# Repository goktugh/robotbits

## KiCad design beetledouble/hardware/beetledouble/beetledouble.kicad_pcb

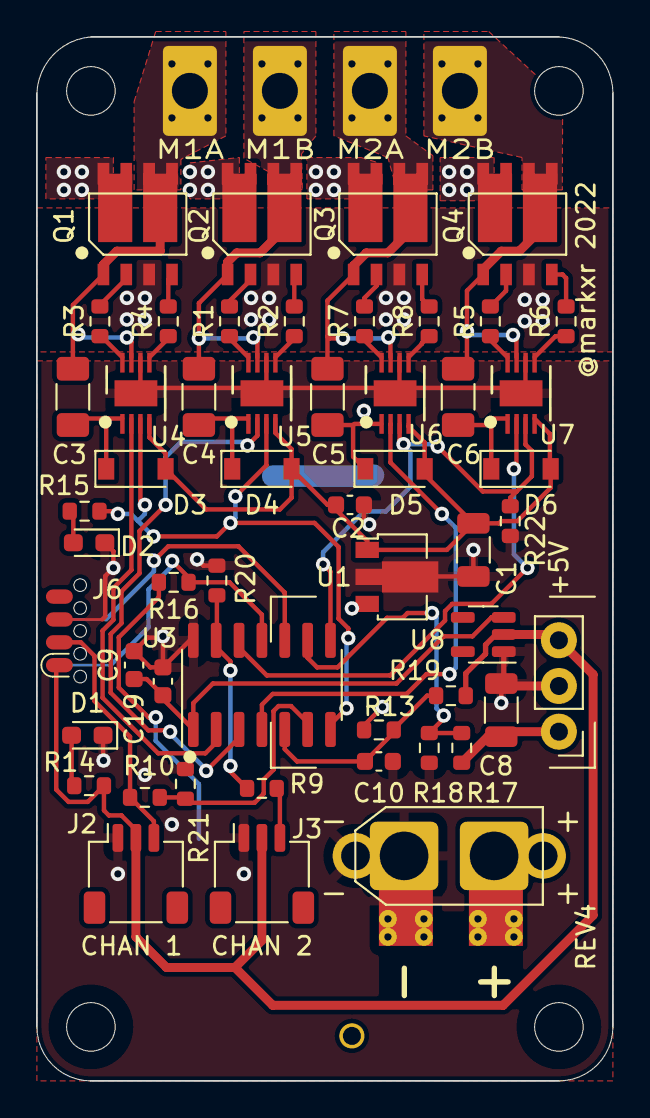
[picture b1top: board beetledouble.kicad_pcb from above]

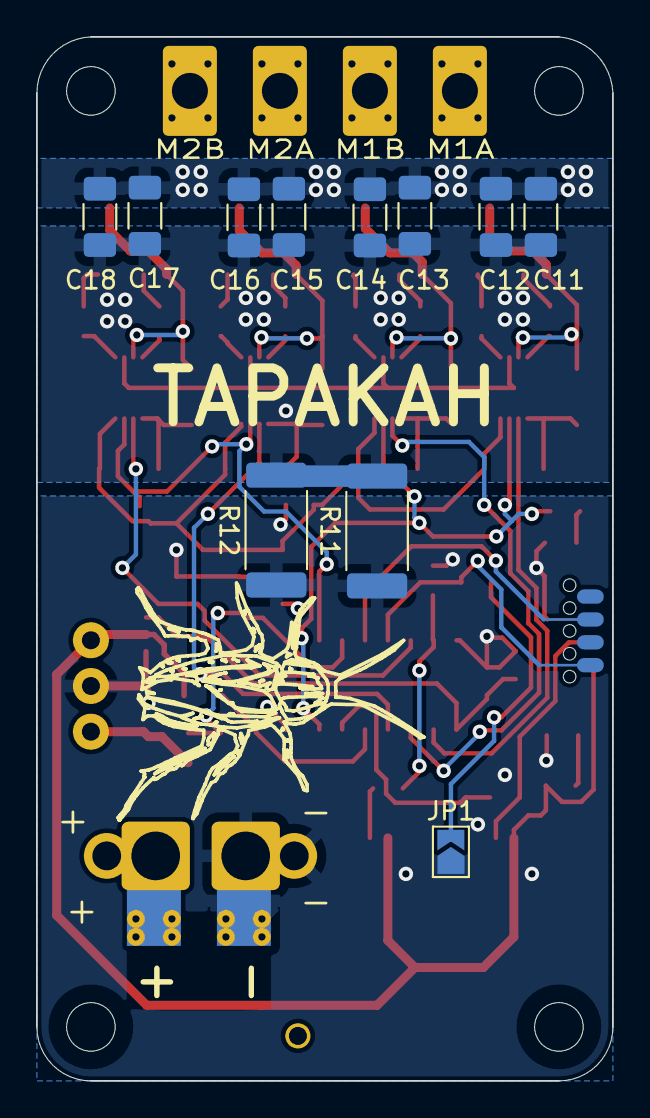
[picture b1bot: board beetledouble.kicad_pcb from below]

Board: 4 copper layers, 32.0 x 58.0 mm, 69 parts (11 on the bottom side), 47 nets.

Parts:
C1, C8: 10uF 50V; C_1206_3216Metric
C2, C9, C10: 2.2uF 50V; C_0603_1608Metric
C3, C4, C5, C6: 4.7uF 50V; C_1206_3216Metric_Pad1.33x1.80mm_HandSolder
C11, C12, C14, C15: 10uF 50V; C_1206_3216Metric_Pad1.33x1.80mm_HandSolder
C13, C16, C17, C18: DNP; C_1206_3216Metric_Pad1.33x1.80mm_HandSolder
C19: 100nF; C_0603_1608Metric
D1, D2: LED; LED_0603_1608Metric_Pad1.05x0.95mm_HandSolder
D3, D4, D5, D6: B5819W; D_SOD-123
H1, H2, H3, H4: MountingHole; MountingHole_2.7mm_M2.5
J1: XT30PW-M; beetlepower
J2, J3: JST-SH; JST_SH_SM03B-SRSS-TB_1x03-1MP_P1.00mm_Horizontal
J4, J5: motor_out; beetlemotor
J6: prog connector; SOIC_clipProgSmall
JP1: CONFIG1; SolderJumper-2_P1.3mm_Open_TrianglePad1.0x1.5mm
Q1, Q2, Q3, Q4: SE3082G; Infineon-PG-TDSON
R1, R2, R3, R4, R5, R6, R7, R8: 15R; R_0603_1608Metric
R9, R10, R13, R14, R15, R18: 1k; R_0603_1608Metric
R11, R12: 0.01 ohm; R_2512_6332Metric_Pad1.40x3.35mm_HandSolder
R16, R17, R19: 22k; R_0603_1608Metric
R20, R21, R22: 100k; R_0603_1608Metric
U1: 78L12G-AB3-R; SOT-89-3
U2: DD4012SB; aliexpress_regulator_3p
U3: ATtiny1614-SS; SOIC-14_3.9x8.7mm_P1.27mm
U4, U5, U6, U7: NCP81155MN; DFN-8-3x3mm_hand1
U8: HT7550-2; SOT-23-5

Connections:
+5V: J2.2, J3.2, J6.1, R14.2, R19.1, U2.3 (VOUT), U8.2 (VIN)
+12V: C1.1, C2.1, D3.2 (A), D4.2 (A), D5.2 (A), D6.2 (A), U1.1 (OUT), U4.4 (VCC), U5.4 (VCC), U6.4 (VCC), U7.4 (VCC)
/CONFIG1: JP1.2 (B), R16.1
/ISENSE: C10.1, R13.2, R19.2, U3.5 (PA7)
/MCUPOWER: C9.1, C19.1, U3.1 (VCC), U8.3 (VOUT)
/P1: J2.3, J6.2, R10.1
/P2: J3.3, R9.1
/VSENSE: R17.2, R18.2, U3.9 (PB0)
/driver1/BOOST1: C3.1, D3.1 (K), U4.1 (BST)
/driver1/BOOST2: C4.1, D4.1 (K), U5.1 (BST)
/driver1/GATEH1: Q1.2 (G), R3.2
/driver1/GATEH2: Q2.2 (G), R1.2
/driver1/GATEL1: Q1.4 (G), R4.2
/driver1/GATEL2: Q2.4 (G), R2.2
/driver1/MOTORH1: R3.1, U4.8 (DRVH)
/driver1/MOTORH2: R1.1, U5.8 (DRVH)
/driver1/MOTORL1: R4.1, U4.5 (DRVL)
/driver1/MOTORL2: R2.1, U5.5 (DRVL)
/driver1/MOTORS1: C3.2, J4.1, Q1.1 (S), Q1.5 (D), Q1.6 (G), U4.7 (SW)
/driver1/MOTORS2: C4.2, J4.2, Q2.1 (S), Q2.5 (D), Q2.6 (G), U5.7 (SW)
/driver2/BOOST1: C5.1, D5.1 (K), U6.1 (BST)
/driver2/BOOST2: C6.1, D6.1 (K), U7.1 (BST)
/driver2/GATEH1: Q3.2 (G), R7.2
/driver2/GATEH2: Q4.2 (G), R5.2
/driver2/GATEL1: Q3.4 (G), R8.2
/driver2/GATEL2: Q4.4 (G), R6.2
/driver2/MOTORH1: R7.1, U6.8 (DRVH)
/driver2/MOTORH2: R5.1, U7.8 (DRVH)
/driver2/MOTORL1: R8.1, U6.5 (DRVL)
/driver2/MOTORL2: R6.1, U7.5 (DRVL)
/driver2/MOTORS1: C5.2, J5.1, Q3.1 (S), Q3.5 (D), Q3.6 (G), U6.7 (SW)
/driver2/MOTORS2: C6.2, J5.2, Q4.1 (S), Q4.5 (D), Q4.6 (G), U7.7 (SW)
GND: C1.2, C2.2, C8.2, C9.2, C10.2, C19.2, D1.1 (K), D2.1 (K), J1.1, J2.1, J3.1, J6.3, JP1.1 (A), R11.1, R12.1, R18.1, R20.2, R21.2, R22.2, U1.2 (GND), U2.2 (GND), U3.14 (GND), U4.6 (GND), U4.9 (FLAG), U5.6 (GND), U5.9 (FLAG), U6.6 (GND), U6.9 (FLAG), U7.6 (GND), U7.9 (FLAG), U8.1 (GND)
GNDSHUNT: C11.2, C12.2, C13.2, C14.2, C15.2, C16.2, C17.2, C18.2, Q1.3 (S), Q2.3 (S), Q3.3 (S), Q4.3 (S), R11.2, R12.2, R13.1
MOTORF_1: U3.2 (PA4), U4.2 (PWM)
MOTORF_2: U3.4 (PA6), U6.2 (PWM)
MOTORR_1: U3.3 (PA5), U5.2 (PWM)
MOTORR_2: U3.12 (PA2), U7.2 (PWM)
MOTOR_ENABLE_1: R15.2, U3.7 (PB2), U4.3 (EN), U5.3 (EN)
MOTOR_ENABLE_2: R22.1, U3.8 (PB1), U6.3 (EN), U7.3 (EN)
unnamed: D1.2 (A), R14.1
unnamed: D2.2 (A), R15.1
PWMIN_1: R10.2, R21.1, U3.6 (PB3)
PWMIN_2: R9.2, R20.1, U3.13 (PA3)
TXDEBUG: J6.8, R16.2, U3.11 (PA1)
UPDI: J6.6, U3.10 (~RESET/PA0)
VBAT: C8.1, C11.1, C12.1, C13.1, C14.1, C15.1, C16.1, C17.1, C18.1, J1.2, Q1.7 (D), Q1.8 (G), Q2.7 (D), Q2.8 (G), Q3.7 (D), Q3.8 (G), Q4.7 (D), Q4.8 (G), R17.1, U1.3 (IN), U2.1 (VIN)

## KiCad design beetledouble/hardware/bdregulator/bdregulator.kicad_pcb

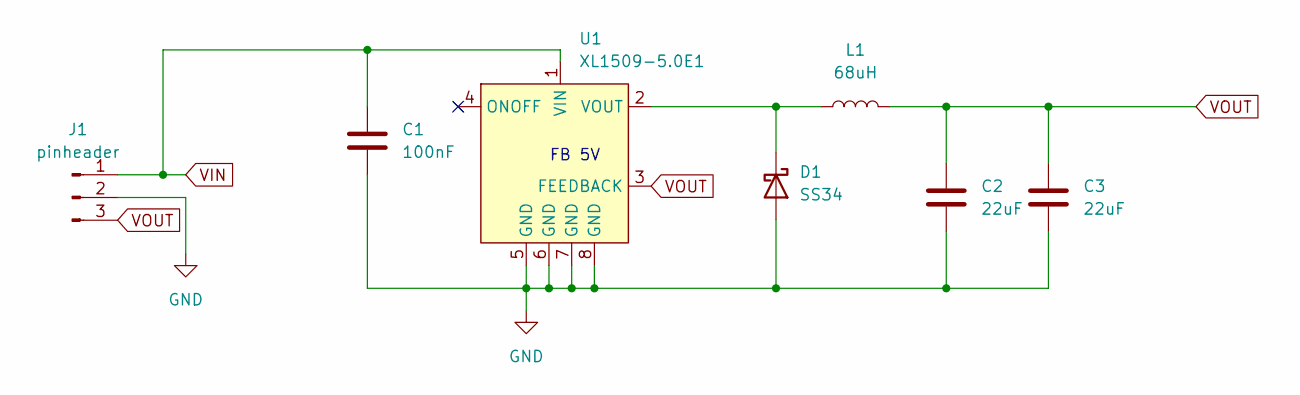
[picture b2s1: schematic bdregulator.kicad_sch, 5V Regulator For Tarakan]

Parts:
C1: 100nF; C_0603_1608Metric; LCSC C14663
C2, C3: 22uF; C_1206_3216Metric; LCSC C5672
D1: SS34; D_SMA; LCSC C8678
J1: pinheader; PinHeader_1x03_P2.54mm_Vertical
L1: 68uH; L_12x12mm_H4.5mm; LCSC C149549
U1: XL1509-5.0E1; SOIC-8_3.9x4.9mm_P1.27mm; LCSC C61063

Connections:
GND: C1.2, C2.2, C3.2, D1.2 (A), J1.2, U1.5 (GND), U1.6 (GND), U1.7 (GND), U1.8 (GND)
unnamed: D1.1 (K), L1.1, U1.2 (VOUT)
VIN: C1.1, J1.1, U1.1 (VIN)
VOUT: C2.1, C3.1, J1.3, L1.2, U1.3 (FEEDBACK)

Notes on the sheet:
FB 5V

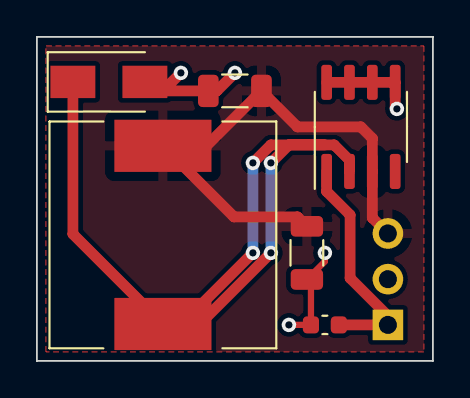
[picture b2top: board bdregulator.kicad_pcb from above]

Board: 2 copper layers, 22.0 x 18.0 mm, 7 parts (1 on the bottom side), 4 nets.

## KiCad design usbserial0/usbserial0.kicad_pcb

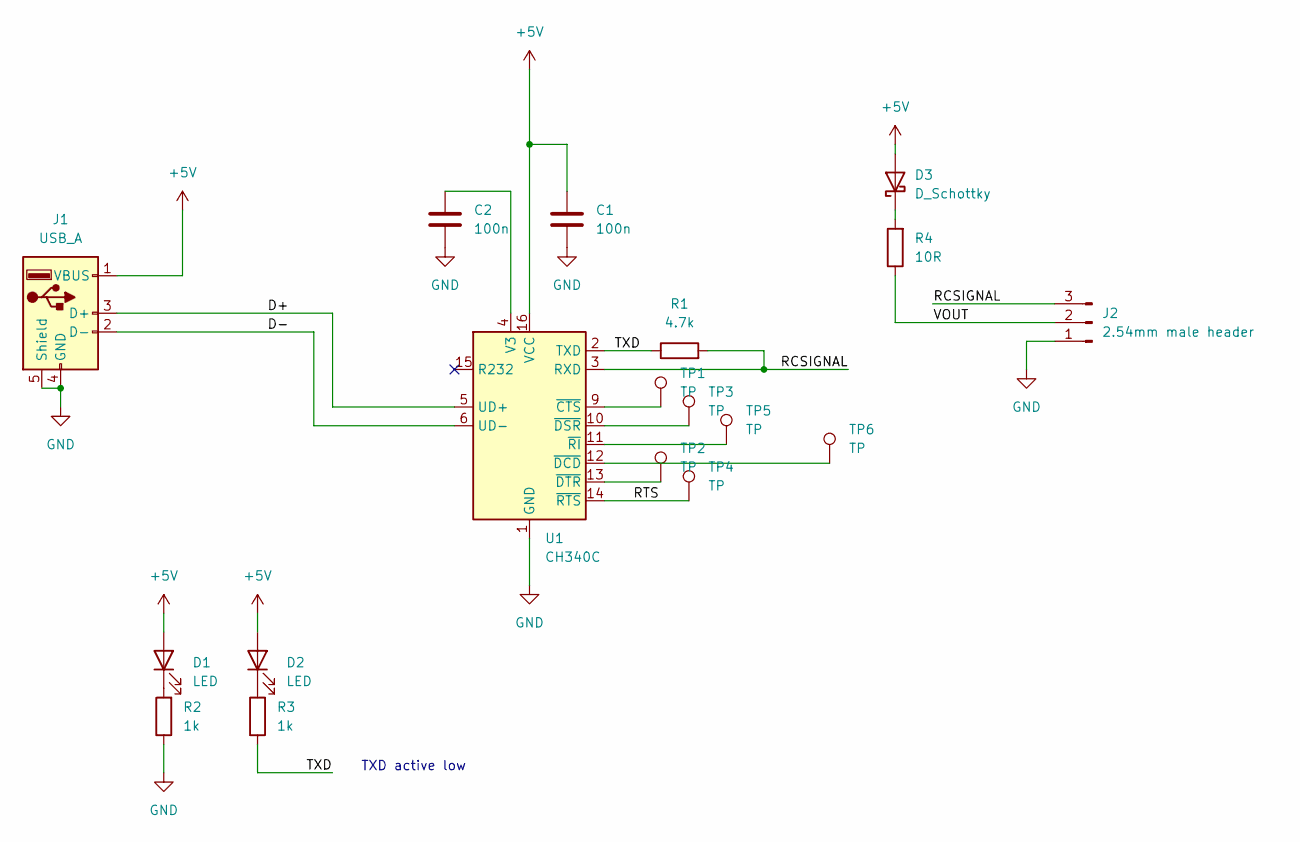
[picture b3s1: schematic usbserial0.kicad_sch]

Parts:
C1, C2: 100n; C_0805_2012Metric_Pad1.18x1.45mm_HandSolder; LCSC C49678
D1, D2: LED; LED_0805_2012Metric_Pad1.15x1.40mm_HandSolder; LCSC C2296
D3: D_Schottky; D_SOD-123; LCSC C8598
J1: USB_A; USB_A_CNCTech_1001-011-01101_Horizontal; MPN U-G-04WS-W-03; LCSC C283548
J2: 2.54mm male header; PinHeader_1x03_P2.54mm_Horizontal
R1: 4.7k; R_0805_2012Metric_Pad1.20x1.40mm_HandSolder; LCSC C17673
R2, R3: 1k; R_0805_2012Metric_Pad1.20x1.40mm_HandSolder; LCSC C17513
R4: 10R; R_0805_2012Metric_Pad1.20x1.40mm_HandSolder; LCSC C17415
TP1, TP2, TP3, TP4, TP5, TP6: TP; TestPoint_Pad_D2.0mm
U1: CH340C; SOIC-16_3.9x9.9mm_P1.27mm; LCSC C84681

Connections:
+5V: C1.1, D1.2 (A), D2.2 (A), D3.2 (A), J1.1 (VBUS), U1.16 (VCC)
/D+: J1.3 (D+), U1.5 (UD+)
/D-: J1.2 (D-), U1.6 (UD-)
/RCSIGNAL: J2.3, R1.2, U1.3 (RXD)
/RTS: TP4.1, U1.14 (~RTS)
/TXD: R1.1, R3.1, U1.2 (TXD)
/VOUT: J2.2, R4.1
GND: C1.2, C2.2, J1.4 (GND), J1.5 (Shield), J2.1, R2.1, U1.1 (GND)
unnamed: C2.1, U1.4 (V3)
unnamed: D1.1 (K), R2.2
unnamed: D2.1 (K), R3.2
unnamed: D3.1 (K), R4.2
unnamed: TP1.1, U1.9 (~CTS)
unnamed: TP2.1, U1.13 (~DTR)
unnamed: TP3.1, U1.10 (~DSR)
unnamed: TP5.1, U1.11 (~RI)
unnamed: TP6.1, U1.12 (~DCD)

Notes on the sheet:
TXD active low

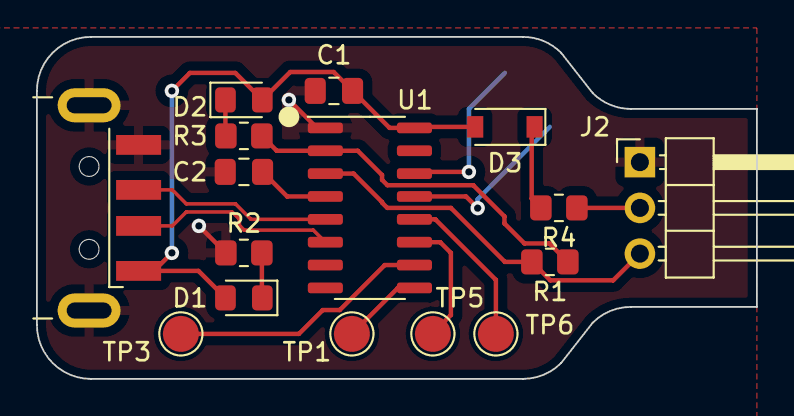
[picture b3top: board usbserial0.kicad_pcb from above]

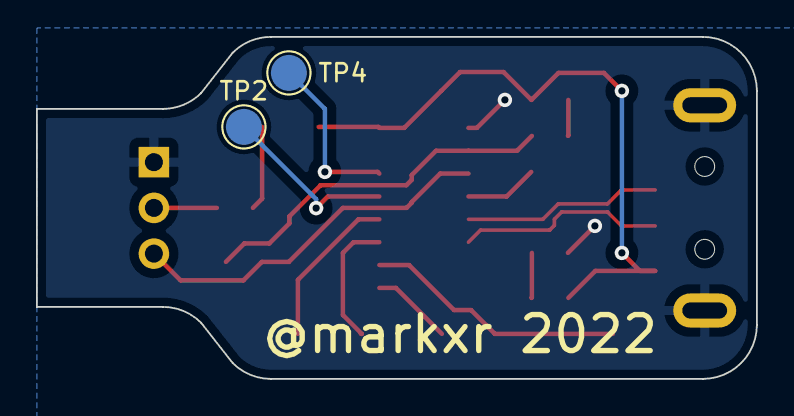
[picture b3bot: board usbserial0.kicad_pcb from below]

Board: 2 copper layers, 40.0 x 19.0 mm, 18 parts (2 on the bottom side), 17 nets.

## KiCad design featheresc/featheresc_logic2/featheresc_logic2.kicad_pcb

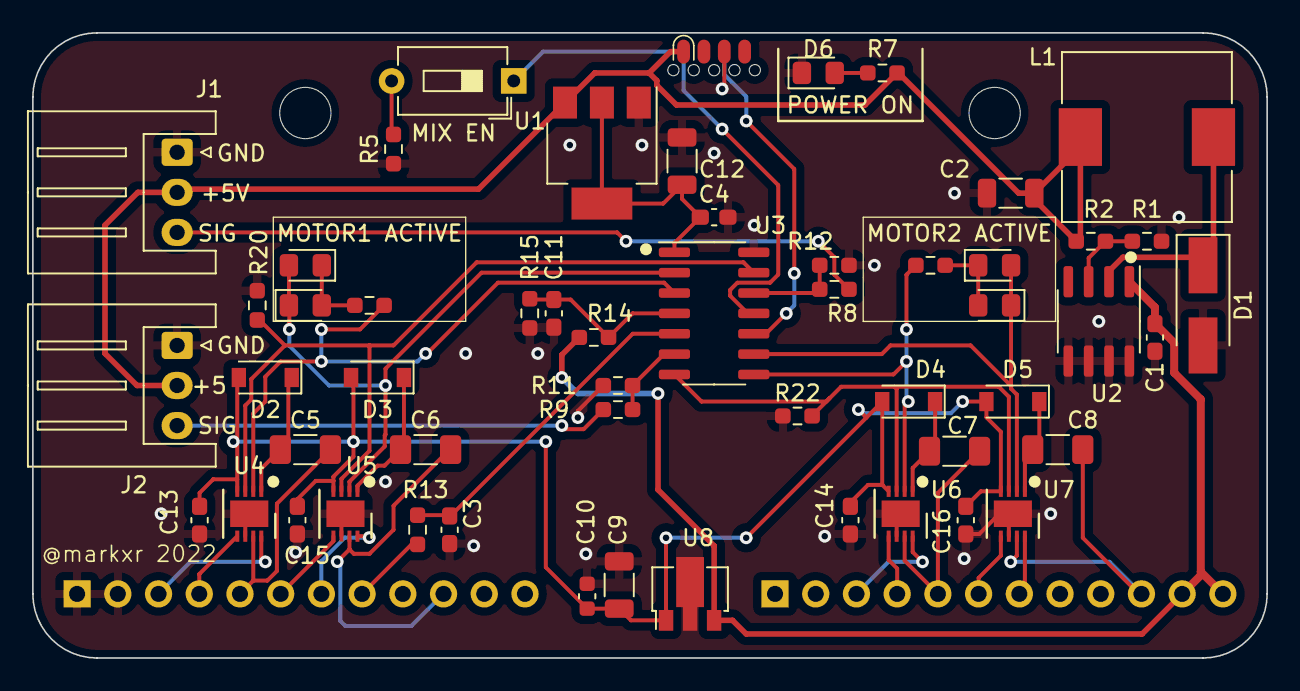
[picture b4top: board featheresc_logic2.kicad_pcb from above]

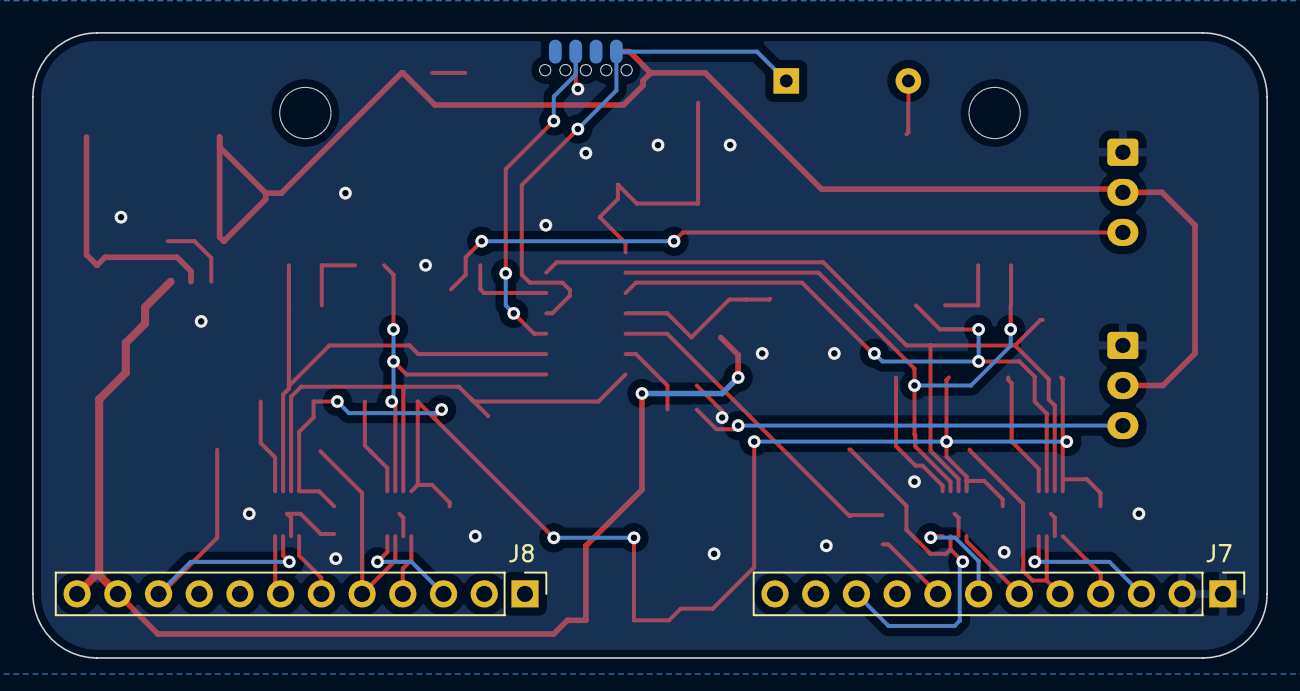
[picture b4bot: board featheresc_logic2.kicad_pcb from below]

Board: 2 copper layers, 77.0 x 39.0 mm, 58 parts (2 on the bottom side), 42 nets.

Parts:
C1, C4, C13, C14, C15, C16: 100 nF; C_0603_1608Metric_Pad1.08x0.95mm_HandSolder
C2, C12: 10uF; C_1206_3216Metric
C3, C11: DNP; C_0603_1608Metric_Pad1.08x0.95mm_HandSolder
C5, C6, C7, C8: 4.7uF 50V; C_1206_3216Metric_Pad1.33x1.80mm_HandSolder
C9: 10uF 50V; C_1206_3216Metric
C10: DNP; C_0603_1608Metric
D1: SS34; D_SMA_Handsoldering
D2, D3, D4, D5: B5819W; D_SOD-123
D6, D9, D10: Green; LED_0805_2012Metric_Pad1.15x1.40mm_HandSolder
D7, D8: Red; LED_0805_2012Metric_Pad1.15x1.40mm_HandSolder
H1, H2: Interconnect M3; MountingHole_3.2mm_M3
J1: RC IN 1; JST_XH_S3B-XH-A_1x03_P2.50mm_Horizontal
J2: RC IN 2; JST_XH_S3B-XH-A_1x03_P2.50mm_Horizontal
J3: soicbite prog connector; SOIC_clipProgSmall
J7: Interconnect 1; PinHeader_1x12_P2.54mm_Vertical
J8: Interconnect 2; PinHeader_1x12_P2.54mm_Vertical
L1: 68uH; L_10.4x10.4_H4.8
R1: 10k; R_0603_1608Metric_Pad0.98x0.95mm_HandSolder
R2, R5, R14, R20, R22: 33k; R_0603_1608Metric_Pad0.98x0.95mm_HandSolder
R3, R4, R7, R8, R9, R13, R15: 1k; R_0603_1608Metric_Pad0.98x0.95mm_HandSolder
R11, R12: 100k; R_0603_1608Metric_Pad0.98x0.95mm_HandSolder
SW1: SW_DIP_x01; SW_DIP_SPSTx01_Slide_6.7x4.1mm_W7.62mm_P2.54mm_LowProfile
U1: AMS1117-50; SOT-223-3_TabPin2
U2: XL1509-ADJE1; SOIC-8_3.9x4.9mm_P1.27mm
U3: ATtiny1614-SS; SOIC-14_3.9x8.7mm_P1.27mm
U4, U5, U6, U7: NCP81155MN; DFN-8-1EP_3x3mm_P0.5mm_EP1.66x2.38mm
U8: 78L12G-AB3-R; SOT-89-3

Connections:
+12V: C9.1, C10.1, C13.1, C14.1, C15.1, C16.1, D2.2 (A), D3.2 (A), D4.2 (A), D5.2 (A), U4.4 (VCC), U5.4 (VCC), U6.4 (VCC), U7.4 (VCC), U8.1 (OUT)
/GATEH11: J7.3, U4.8 (DRVH)
/GATEH12: J8.3, U6.8 (DRVH)
/GATEH21: J7.7, U5.8 (DRVH)
/GATEH22: J8.7, U7.8 (DRVH)
/GATEL11: J7.4, U4.5 (DRVL)
/GATEL12: J8.4, U6.5 (DRVL)
/GATEL21: J7.6, U5.5 (DRVL)
/GATEL22: J8.6, U7.5 (DRVL)
/ISENSE_IN: C3.1, R13.1, U3.5 (PA7)
/MCUPOWER: C4.1, C12.1, U1.2 (VO), U3.1 (VCC)
/MOTOREN_1: R20.2, U3.13 (PA3), U4.3 (EN), U5.3 (EN)
/MOTOREN_2: R22.2, U3.7 (PB2), U6.3 (EN), U7.3 (EN)
/MOTORF_1: R3.2, U3.3 (PA5), U4.2 (PWM)
/MOTORF_2: R4.2, U3.8 (PB1), U6.2 (PWM)
/MOTORR_1: D7.1 (K), D9.2 (A), U3.2 (PA4), U5.2 (PWM)
/MOTORR_2: D8.1 (K), D10.2 (A), U3.9 (PB0), U7.2 (PWM)
/PHASE11: C5.2, J7.5, U4.7 (SW)
/PHASE12: C7.2, J8.5, U6.7 (SW)
/PHASE21: C6.2, J7.10, U5.7 (SW)
/PHASE22: C8.2, J8.10, U7.7 (SW)
/REGSW: D1.1 (K), L1.1, U2.2 (VOUT)
/RXIN_1: J1.3, R8.2
/RXIN_2: J2.3, R9.2
/TXDEBUG: J3.8, SW1.1, U3.11 (PA1)
/UPDI: J3.6, U3.10 (~RESET/PA0)
/VSENSE_IN: C11.1, R14.1, R15.2, U3.4 (PA6)
/gatedrivers1/BOOST1: C5.1, D2.1 (K), U4.1 (BST)
/gatedrivers1/BOOST2: C6.1, D3.1 (K), U5.1 (BST)
/gatedrivers2/BOOST1: C7.1, D4.1 (K), U6.1 (BST)
/gatedrivers2/BOOST2: C8.1, D5.1 (K), U7.1 (BST)
GND: C1.2, C2.2, C3.2, C4.2, C9.2, C10.2, C11.2, C12.2, C13.2, C14.2, C15.2, C16.2, D1.2 (A), D6.1 (K), J1.1, J2.1, J3.3, J7.1, J7.2, R1.1, R5.2, R11.1, R12.1, R15.1, R20.1, R22.1, U1.1 (GND), U2.5 (GND), U2.6 (GND), U2.7 (GND), U2.8 (GND), U3.14 (GND), U4.6 (GND), U4.9 (FLAG), U5.6 (GND), U5.9 (FLAG), U6.6 (GND), U6.9 (FLAG), U7.6 (GND), U7.9 (FLAG), U8.2 (GND)
GNDSHUNT: J7.8, R13.2
unnamed: D6.2 (A), R7.1
unnamed: D7.2 (A), D9.1 (K), R3.1
unnamed: D8.2 (A), D10.1 (K), R4.1
unnamed: R1.2, R2.1, U2.3 (FEEDBACK)
unnamed: R5.1, SW1.2
unnamed: R9.1, R11.2, U3.6 (PB3)
unnamed: R8.1, R12.2, U3.12 (PA2)
VBAT: C1.1, J8.11, J8.12, R14.2, U2.1 (VIN), U8.3 (IN)
VBEC: C2.1, J1.2, J2.2, J3.1, L1.2, R2.2, R7.2, U1.3 (VI)

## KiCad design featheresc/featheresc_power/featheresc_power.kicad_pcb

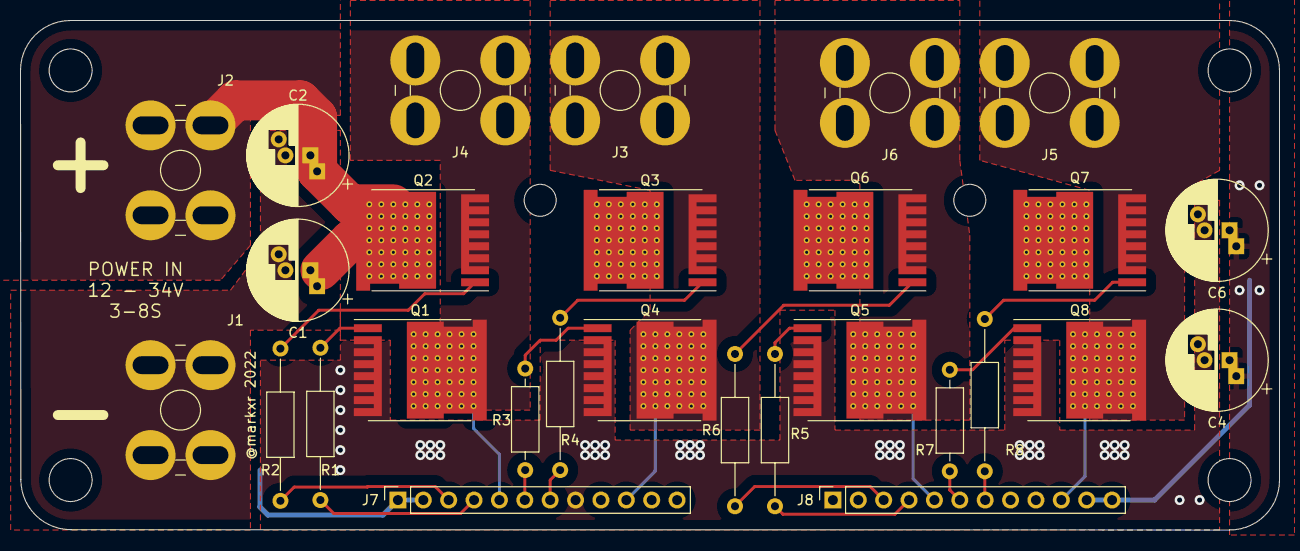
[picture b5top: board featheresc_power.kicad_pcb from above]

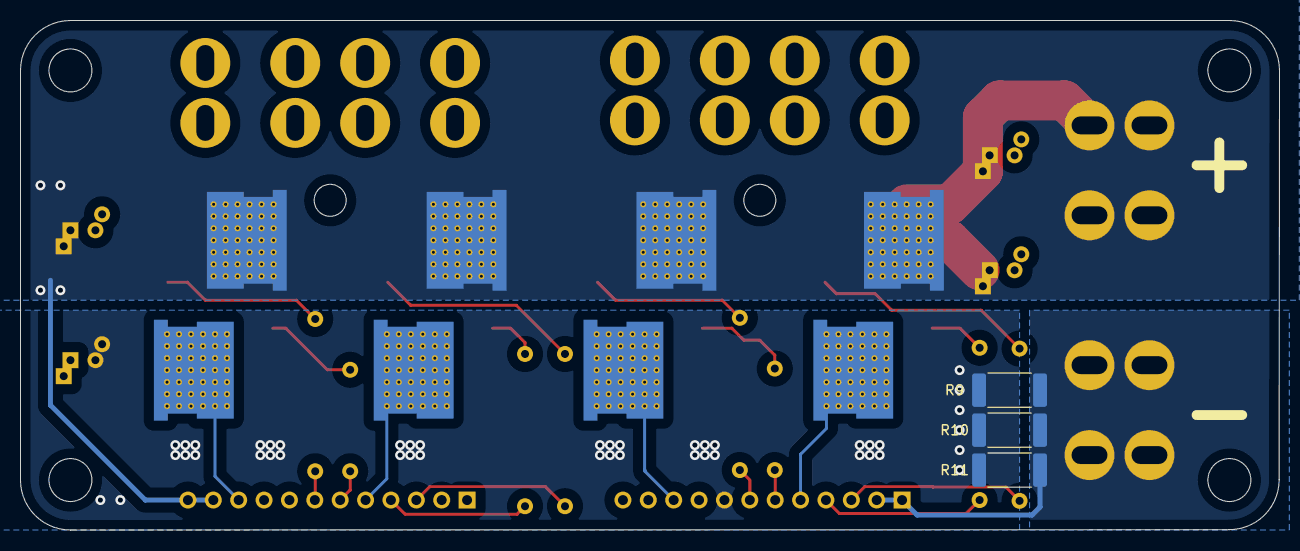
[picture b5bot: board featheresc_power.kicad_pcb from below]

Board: 2 copper layers, 126.0 x 51.0 mm, 37 parts (3 on the bottom side), 23 nets.

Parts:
C1, C2, C4, C6: 120uF; CP_Radial_D10.0mm_P2.50mm_P5.00mm
H1, H2: Interconnect M3; MountingHole_M3_with_standoff
H3, H4, H5, H6: Cornerhole M4; MountingHole_4.3mm_M4
J1: VIN_GND; screwterminal_temile_MFR04425
J2: VIN_POS; screwterminal_temile_MFR04425
J3, J5: PHASE2; screwterminal_temile_MFR04425
J4, J6: PHASE1; screwterminal_temile_MFR04425
J7: interconnect1; PinSocket_1x12_P2.54mm_Vertical
J8: interconnect2; PinSocket_1x12_P2.54mm_Vertical
Q1, Q2, Q3, Q4, Q5, Q6, Q7, Q8: NCEP40T20ALL; Infineon_PG-HSOF-8-1_ThermalVias
R1, R2, R4, R5, R6, R8: 15R; R_Axial_DIN0207_L6.3mm_D2.5mm_P15.24mm_Horizontal
R3, R7: 15R; R_Axial_DIN0207_L6.3mm_D2.5mm_P10.16mm_Horizontal
R9, R10, R11: 2mOhm; R_2512_6332Metric_Pad1.40x3.35mm_HandSolder

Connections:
/GATE1H1: J7.3, R2.1
/GATE1H2: J8.3, R6.1
/GATE1L1: J7.4, R1.1
/GATE1L2: J8.4, R5.1
/GATE2H1: J7.7, R4.1
/GATE2H2: J8.7, R8.1
/GATE2L1: J7.6, R3.1
/GATE2L2: J8.6, R7.1
/PHASE11: J4.1, J7.5, Q1.3 (D), Q2.2 (S)
/PHASE12: J6.1, J8.5, Q5.3 (D), Q6.2 (S)
/PHASE21: J3.1, J7.10, Q3.2 (S), Q4.3 (D)
/PHASE22: J5.1, J8.10, Q7.2 (S), Q8.3 (D)
GND: C1.2, C2.2, J1.1, J7.1, J7.2, R9.1, R10.1, R11.1
GNDSHUNT: C4.2, C6.2, J7.8, Q1.2 (S), Q4.2 (S), Q5.2 (S), Q8.2 (S), R9.2, R10.2, R11.2
unnamed: Q1.1 (G), R1.2
unnamed: Q2.1 (G), R2.2
unnamed: Q3.1 (G), R4.2
unnamed: Q4.1 (G), R3.2
unnamed: Q5.1 (G), R5.2
unnamed: Q6.1 (G), R6.2
unnamed: Q7.1 (G), R8.2
unnamed: Q8.1 (G), R7.2
VBAT: C1.1, C2.1, C4.1, C6.1, J2.1, J8.11, J8.12, Q2.3 (D), Q3.3 (D), Q6.3 (D), Q7.3 (D)

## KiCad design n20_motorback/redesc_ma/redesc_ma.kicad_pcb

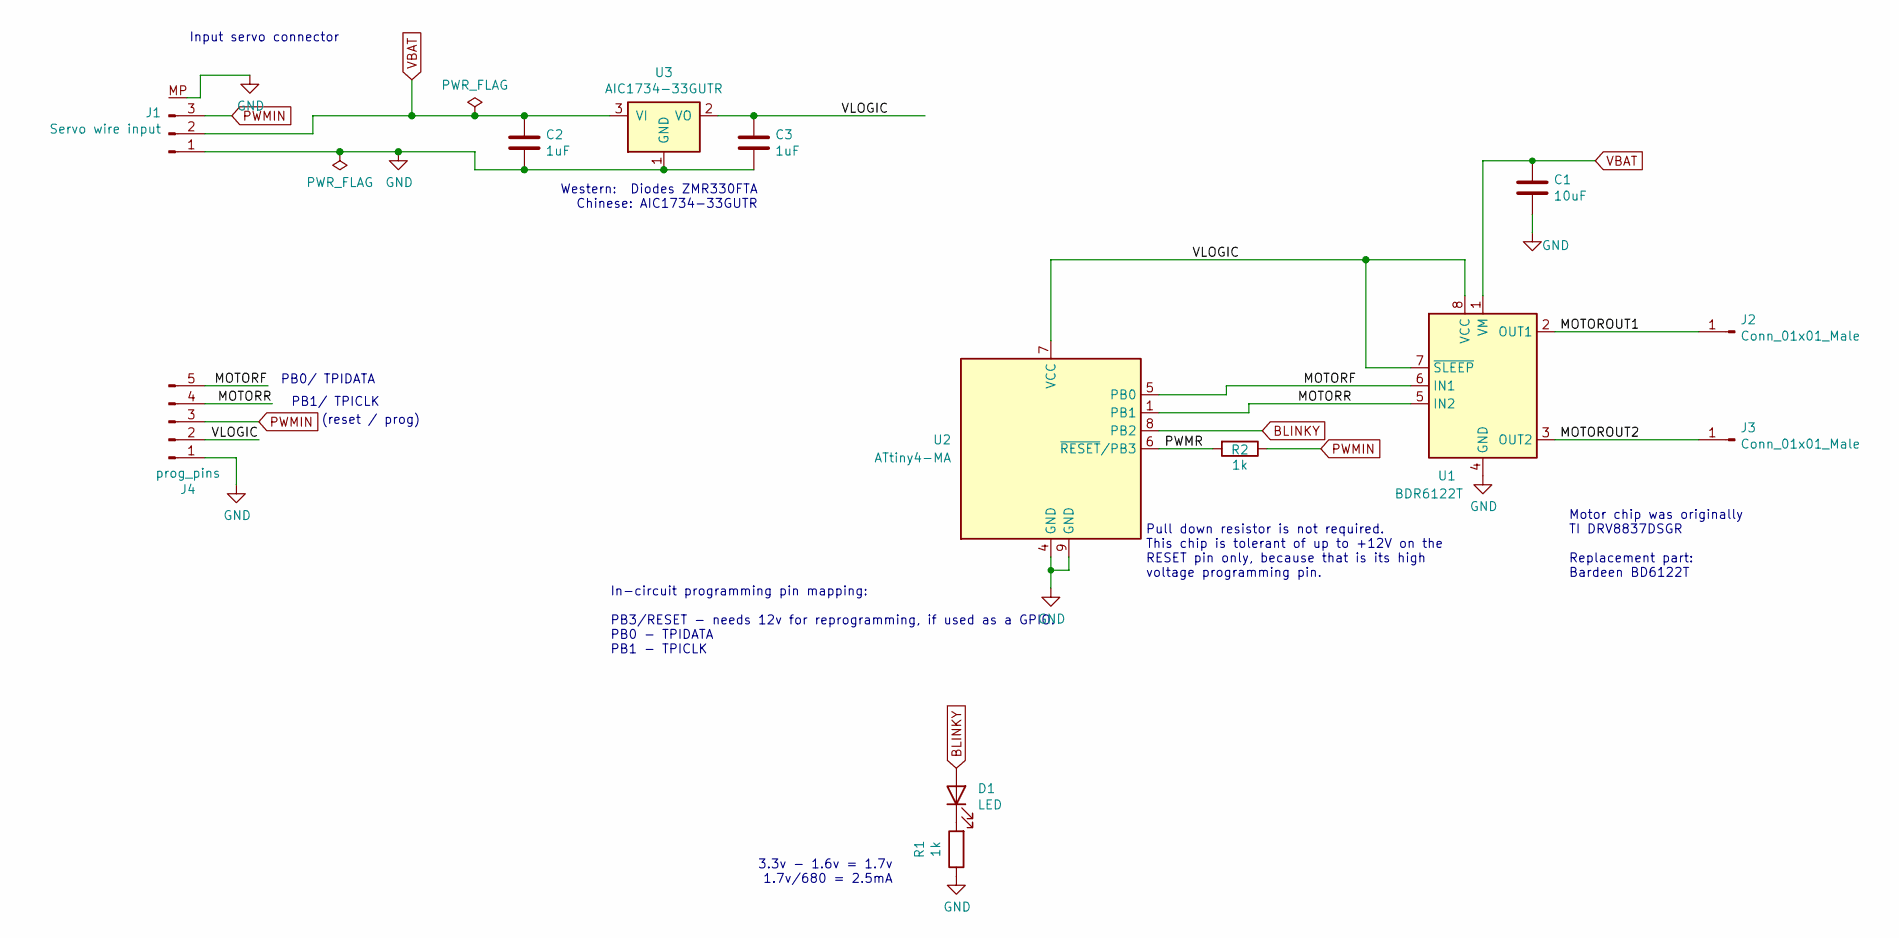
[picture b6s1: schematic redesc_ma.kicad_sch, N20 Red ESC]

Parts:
C1: 10uF; C_0603_1608Metric; MPN CL10A106KP8NNNC; LCSC C19702
C2, C3: 1uF; C_0603_1608Metric
D1: LED; LED_0603_1608Metric; MPN Red LED 0603; LCSC C2286
J1: Servo wire input; JST_SH_SM03B-SRSS-TB_1x03-1MP_P1.00mm_Horizontal; MPN SM03B-SRSS-TB
J2, J3: Conn_01x01_Male; motorpad
J4: prog_pins; pogopins_5
R1, R2: 1k; R_0603_1608Metric; MPN 1k ohm 0603; LCSC C21190
U1: BDR6122T; drv8837_custom; MPN BDR6122T; LCSC C908104
U2: ATtiny4-MA; DFN-8-1EP_2x2mm_P0.5mm_EP0.9x1.5mm
U3: AIC1734-33GUTR; SOT-23; MPN AIC1734-33GUTR; LCSC C211659

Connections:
/MOTORF: J4.5, U1.6 (IN1), U2.5 (PB0)
/MOTOROUT1: J2.1, U1.2 (OUT1)
/MOTOROUT2: J3.1, U1.3 (OUT2)
/MOTORR: J4.4, U1.5 (IN2), U2.1 (PB1)
/PWMR: R2.2, U2.6 (~RESET/PB3)
/VLOGIC: C3.1, J4.2, U1.7 (~SLEEP), U1.8 (VCC), U2.7 (VCC), U3.2 (VO)
BLINKY: D1.2 (A), U2.8 (PB2)
GND: C1.2, C2.2, C3.2, J1.1, J1.MP, J4.1, R1.1, U1.4 (GND), U1.9 (GND), U2.4 (GND), U2.9 (GND), U3.1 (GND)
unnamed: D1.1 (K), R1.2
PWMIN: J1.3, J4.3, R2.1
VBAT: C1.1, C2.1, J1.2, U1.1 (VM), U3.3 (VI)

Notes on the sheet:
Input servo connector
3.3v - 1.6v = 1.7v 1.7v/680 = 2.5mA
In-circuit programming pin mapping: PB3/RESET - needs 12v for reprogramming, if used as a GPIO. PB0 - TPIDATA PB1 - TPICLK
Motor chip was originally TI DRV8837DSGR Replacement part: Bardeen BD6122T
(reset / prog)
PB0/ TPIDATA
PB1/ TPICLK
Pull down resistor is not required. This chip is tolerant of up to +12V on the RESET pin only, because that is its high voltage programming pin.
Western: Diodes ZMR330FTA Chinese: AIC1734-33GUTR

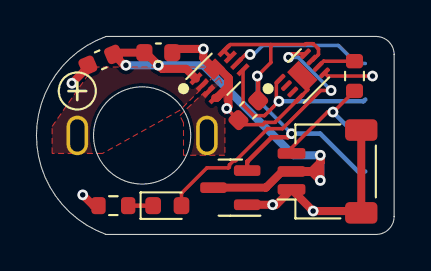
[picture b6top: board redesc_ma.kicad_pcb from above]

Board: 2 copper layers, 19.9 x 11.0 mm, 13 parts (1 on the bottom side), 11 nets.

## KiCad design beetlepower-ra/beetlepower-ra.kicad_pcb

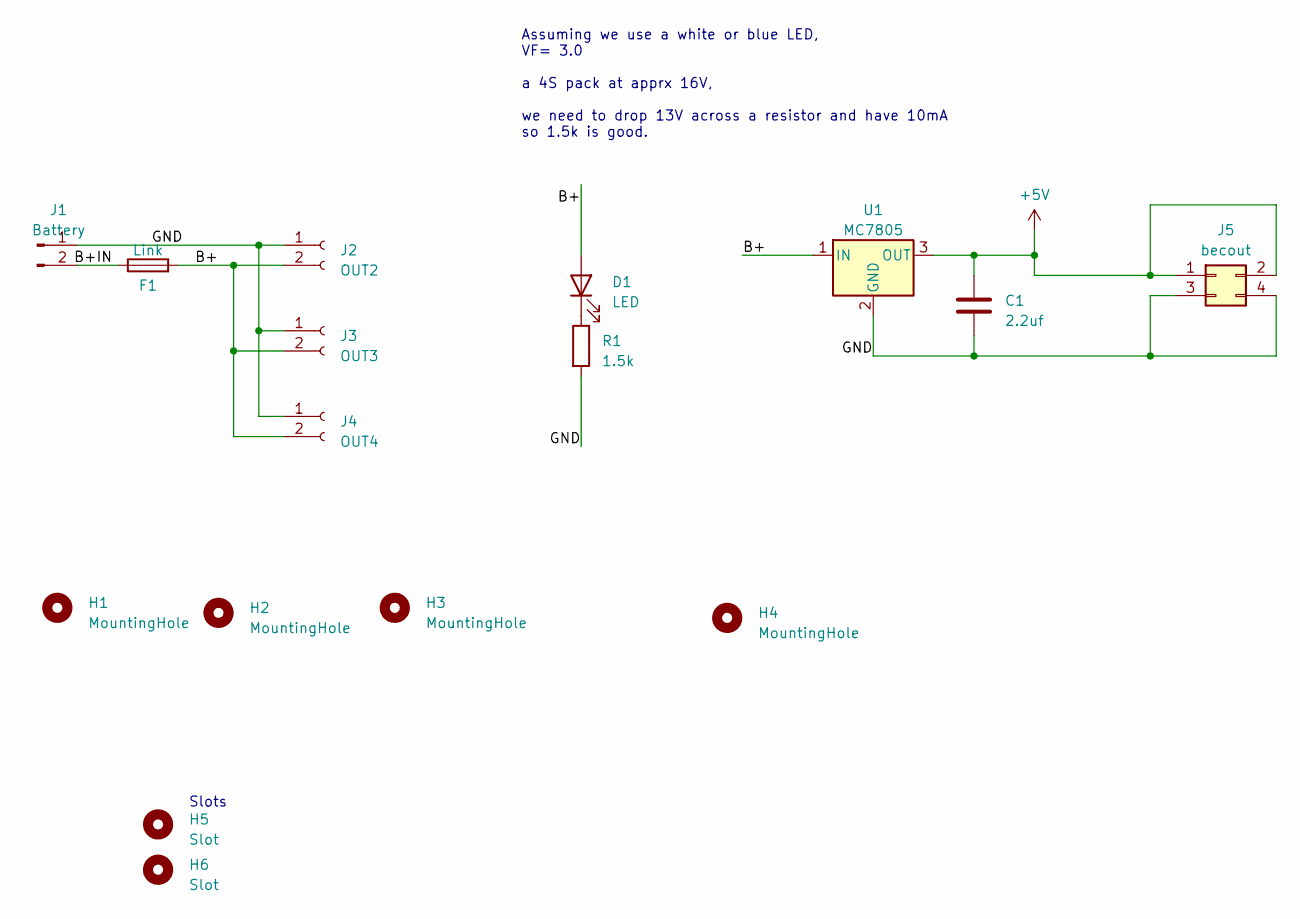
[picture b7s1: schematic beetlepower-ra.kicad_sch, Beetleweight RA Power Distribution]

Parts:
C1: 2.2uf; C_0805_2012Metric_Pad1.18x1.45mm_HandSolder
D1: LED; LED_D5.0mm
F1: Link; AMASS_XT30PW-F_1x02_P2.50mm_Horizontal
H1, H2, H3, H4: MountingHole; MountingHole_3.2mm_M3
H5, H6: Slot; cabletie_slot
J1: Battery; XT30U-M
J2: OUT2; XT30U-F
J3: OUT3; XT30U-F
J4: OUT4; XT30U-F
J5: becout; PinHeader_2x02_P2.54mm_Vertical
R1: 1.5k; R_0805_2012Metric_Pad1.20x1.40mm_HandSolder
U1: MC7805; TO-252-3_TabPin2; LCSC C54285

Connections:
+5V: C1.1, J5.1, J5.2, U1.3 (OUT)
/B+: D1.2 (A), F1.2, J2.2, J3.2, J4.2, U1.1 (IN)
/B+IN: F1.1, J1.2
/GND: C1.2, J1.1, J2.1, J3.1, J4.1, J5.3, J5.4, R1.2, U1.2 (GND)
unnamed: D1.1 (K), R1.1

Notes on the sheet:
Slots
Assuming we use a white or blue LED, VF= 3.0 a 4S pack at apprx 16V, we need to drop 13V across a resistor and have 10mA so 1.5k is good.

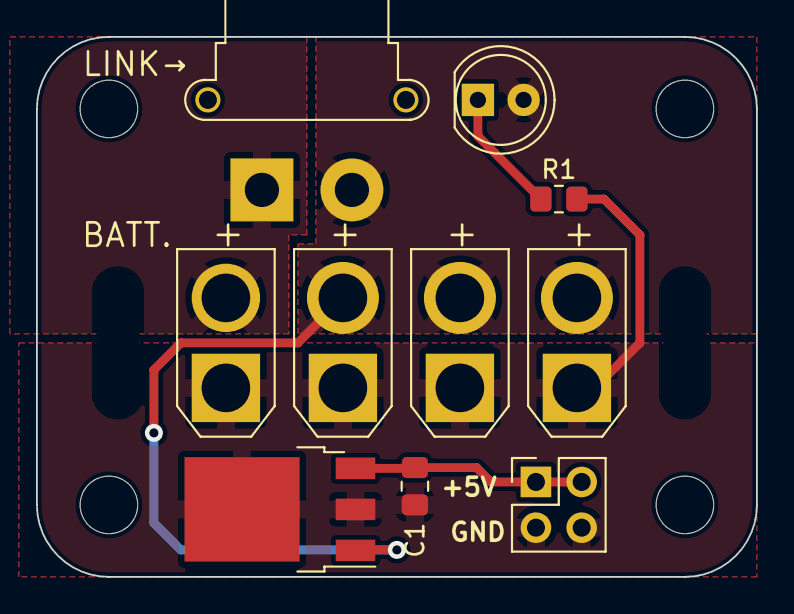
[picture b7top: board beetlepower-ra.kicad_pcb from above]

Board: 2 copper layers, 40.0 x 30.0 mm, 16 parts (0 on the bottom side), 5 nets.

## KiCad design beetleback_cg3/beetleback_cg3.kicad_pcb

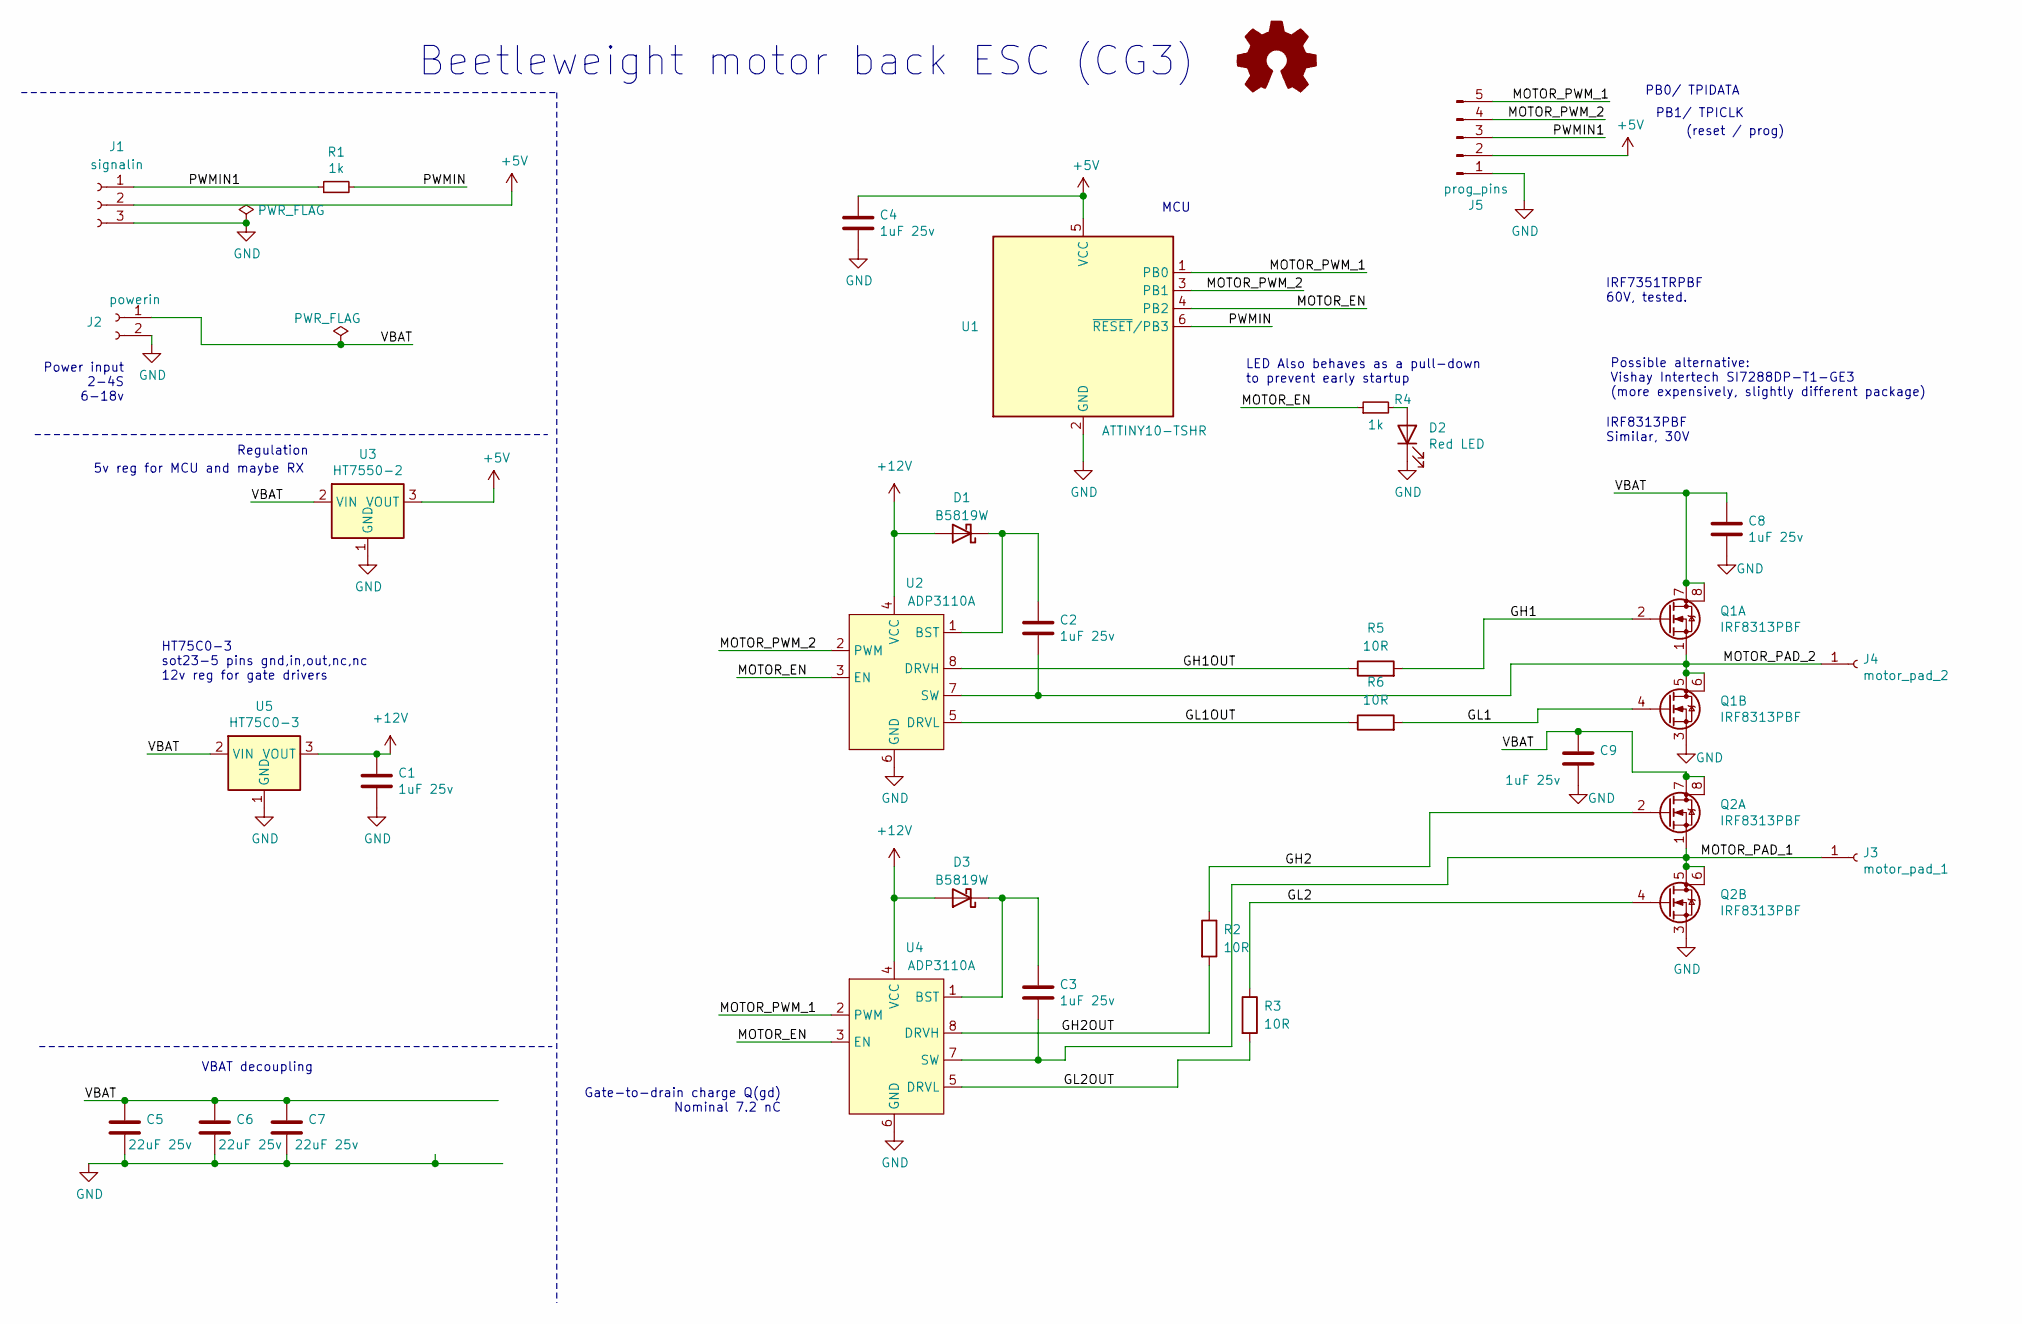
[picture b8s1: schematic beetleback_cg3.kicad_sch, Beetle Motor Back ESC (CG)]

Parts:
C1, C2, C3, C4, C8, C9: 1uF 25v; C_0402_1005Metric; LCSC C52923
C5, C6, C7: 22uF 25v; C_1206_3216Metric; LCSC C12891
D1, D3: B5819W; D_SOD-123; LCSC C8598
D2: Red LED; LED_0603_1608Metric; LCSC C2286
J1: signalin; rx_pins
J2: powerin; beetlepower_in
J3: motor_pad_1; bbb_motorpin
J4: motor_pad_2; bbb_motorpin
J5: prog_pins; pogopins_5
Q1, Q2: IRF8313PBF; SOIC-8_3.9x4.9mm_P1.27mm; LCSC C57696
R1, R4: 1k; R_0402_1005Metric; LCSC C11702
R2, R3, R5, R6: 10R; R_0402_1005Metric; LCSC C25077
U1: ATTINY10-TSHR; SOT-23-6_Handsoldering
U2, U4: ADP3110A; SOIC-8_3.9x4.9mm_P1.27mm; LCSC C82321
U3: HT7550-2; SOT-23-5; LCSC C81799
U5: HT75C0-3; SOT-23-5; LCSC C259861

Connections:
+5V: C4.1, J1.2, J5.2, U1.5 (VCC), U3.3 (VOUT)
+12V: C1.1, D1.2 (A), D3.2 (A), U2.4 (VCC), U4.4 (VCC), U5.3 (VOUT)
/GH1: Q1.2 (G), R5.2
/GH1OUT: R5.1, U2.8 (DRVH)
/GH2: Q2.2 (G), R2.1
/GH2OUT: R2.2, U4.8 (DRVH)
/GL1: Q1.4 (G), R6.2
/GL1OUT: R6.1, U2.5 (DRVL)
/GL2: Q2.4 (G), R3.1
/GL2OUT: R3.2, U4.5 (DRVL)
/MOTOR_EN: R4.1, U1.4 (PB2), U2.3 (EN), U4.3 (EN)
/MOTOR_PAD_1: C3.2, J3.1, Q2.1 (S), Q2.5 (D), Q2.6 (D), U4.7 (SW)
/MOTOR_PAD_2: C2.2, J4.1, Q1.1 (S), Q1.5 (D), Q1.6 (D), U2.7 (SW)
/MOTOR_PWM_1: J5.5, U1.1 (PB0), U4.2 (PWM)
/MOTOR_PWM_2: J5.4, U1.3 (PB1), U2.2 (PWM)
/PWMIN: R1.2, U1.6 (~RESET/PB3)
/PWMIN1: J1.1, J5.3, R1.1
/VBAT: C5.1, C6.1, C7.1, C8.1, C9.1, J2.1, Q1.7 (D), Q1.8 (D), Q2.7 (D), Q2.8 (D), U3.2 (VIN), U5.2 (VIN)
GND: C1.2, C4.2, C5.2, C6.2, C7.2, C8.2, C9.2, D2.1 (K), J1.3, J2.2, J5.1, Q1.3 (S), Q2.3 (S), U1.2 (GND), U2.6 (GND), U3.1 (GND), U4.6 (GND), U5.1 (GND)
unnamed: C2.1, D1.1 (K), U2.1 (BST)
unnamed: C3.1, D3.1 (K), U4.1 (BST)
unnamed: D2.2 (A), R4.2

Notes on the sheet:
Power input 2-4S 6-18v
HT75C0-3 sot23-5 pins gnd,in,out,nc,nc 12v reg for gate drivers
5v reg for MCU and maybe RX
Regulation
VBAT decoupling
Gate-to-drain charge Q(gd) Nominal 7.2 nC
MCU
Beetleweight motor back ESC (CG3)
LED Also behaves as a pull-down to prevent early startup
IRF7351TRPBF 60V, tested.
IRF8313PBF Similar, 30V
Possible alternative: Vishay Intertech SI7288DP-T1-GE3 (more expensively, slightly different package)
PB0/ TPIDATA
PB1/ TPICLK
(reset / prog)
